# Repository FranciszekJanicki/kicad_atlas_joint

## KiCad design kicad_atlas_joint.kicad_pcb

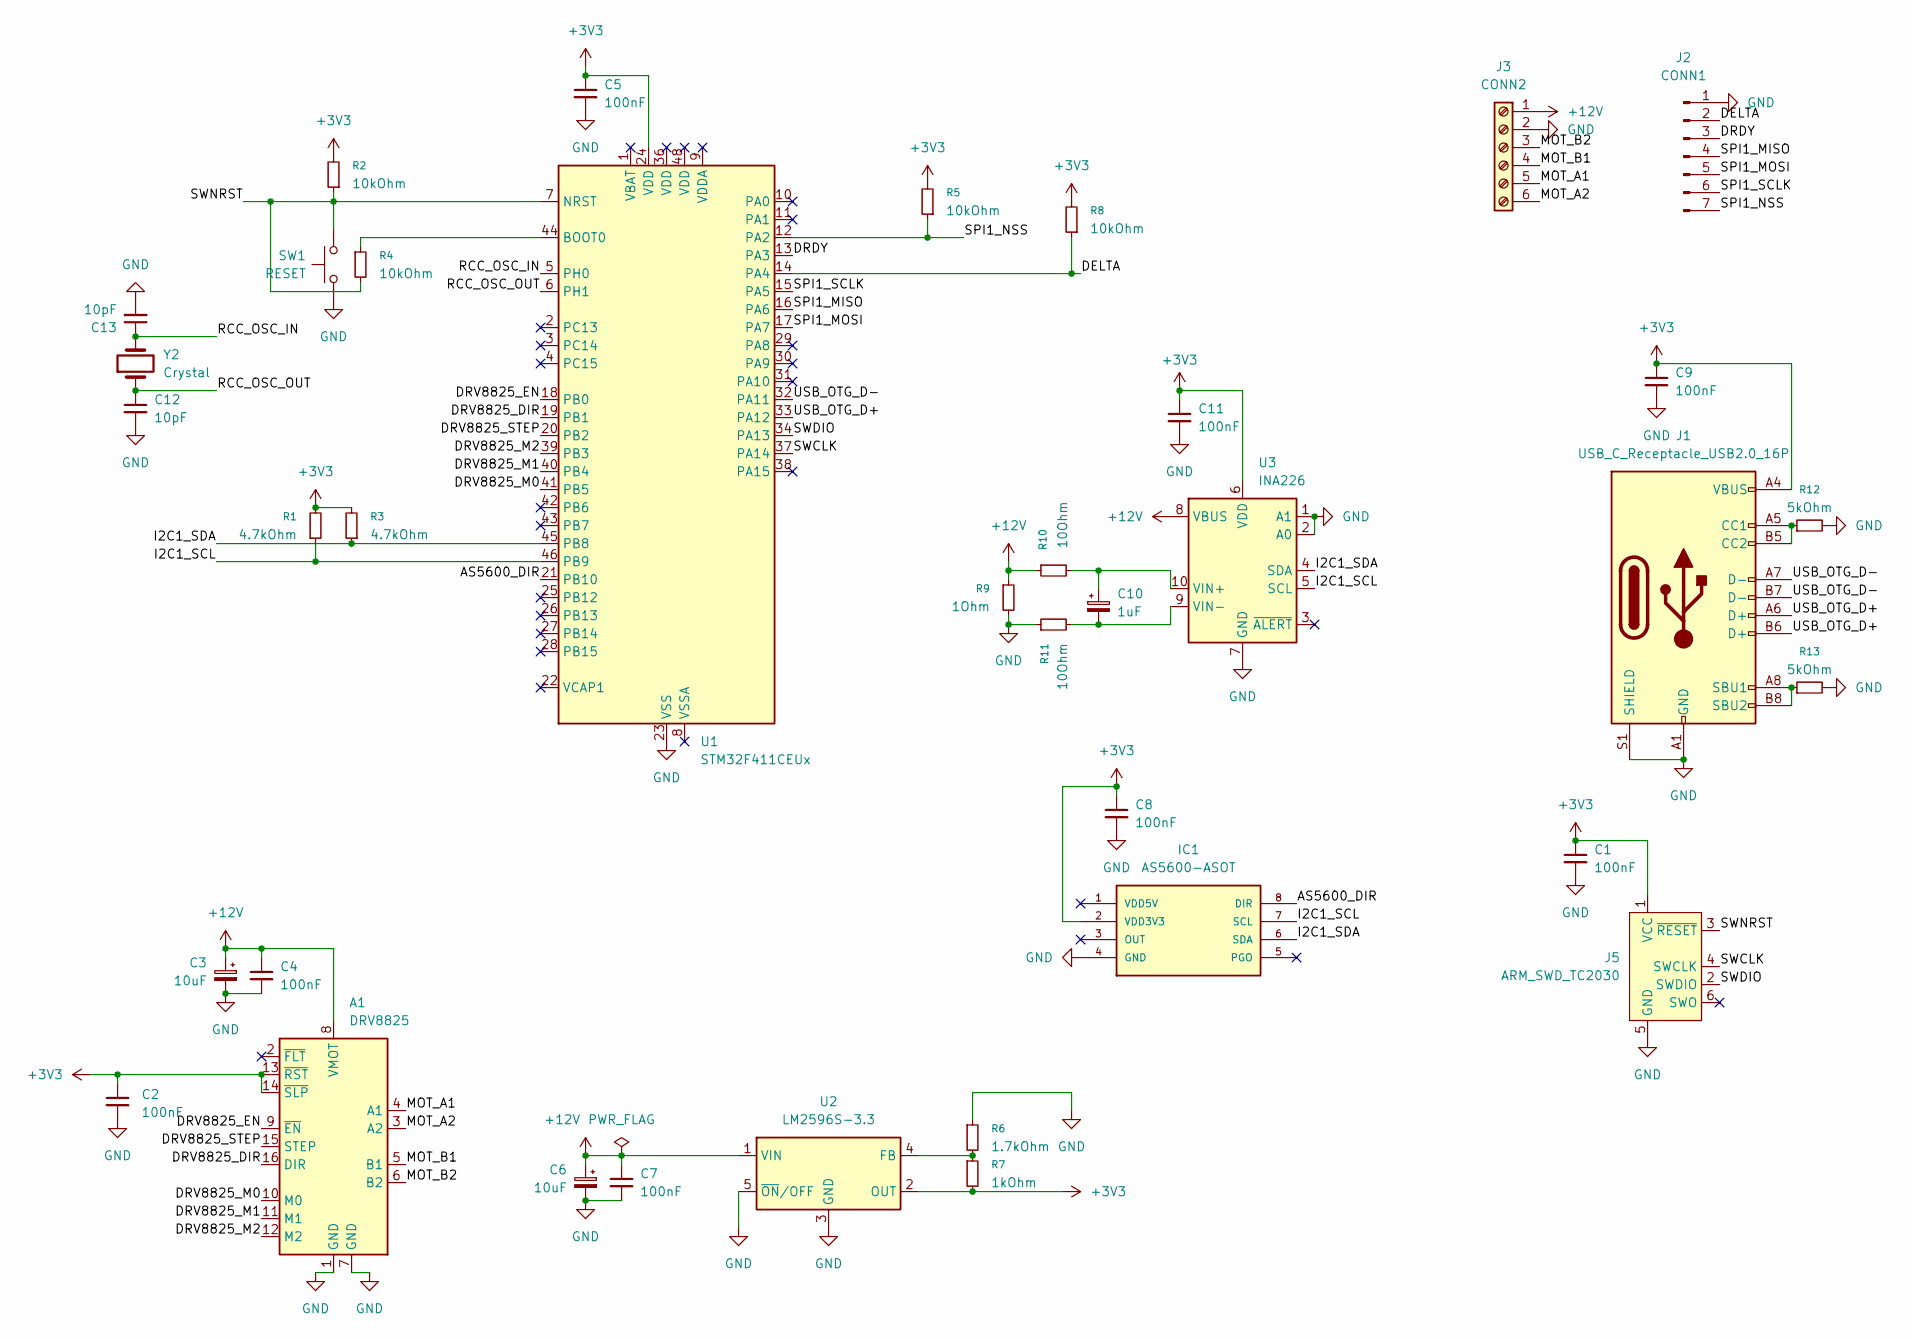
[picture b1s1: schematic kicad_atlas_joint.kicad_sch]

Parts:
A1: DRV8825; Pololu_Breakout-16_15.2x20.3mm
C1, C2, C4, C5, C7, C8, C9, C11: 100nF; C_0201_0603Metric_Pad0.64x0.40mm_HandSolder
C3, C6: 10uF; C_0201_0603Metric_Pad0.64x0.40mm_HandSolder
C10: 1uF; C_0201_0603Metric_Pad0.64x0.40mm_HandSolder
C12, C13: 10pF; C_0201_0603Metric_Pad0.64x0.40mm_HandSolder
IC1: AS5600-ASOT; SOIC127P600X175-8N; MOUSER_PART_NUMBER 985-AS5600-ASOT
J1: USB_C_Receptacle_USB2.0_16P; USB_C_Receptacle_JAE_DX07S016JA1R1500
J2: CONN1; JST_SHL_SM07B-SHLS-TF_1x07-1MP_P1.00mm_Horizontal
J3: CONN2; TerminalBlock_Xinya_XY308-2.54-6P_1x06_P2.54mm_Horizontal
J5: ARM_SWD_TC2030; Tag-Connect_TC2030-IDC-FP_2x03_P1.27mm_Vertical
R1, R3: 4.7kOhm; R_0201_0603Metric
R2, R4, R5, R8: 10kOhm; R_0201_0603Metric
R6: 1.7kOhm; R_0201_0603Metric
R7: 1kOhm; R_0201_0603Metric
R9: 1Ohm; R_0201_0603Metric
R10, R11: 10Ohm; R_0201_0603Metric
R12, R13: 5kOhm; R_0201_0603Metric
SW1: RESET; R_0201_0603Metric
U1: STM32F411CEUx; QFN-48-1EP_7x7mm_P0.5mm_EP5.6x5.6mm
U2: LM2596S-3.3; TO-263-5_TabPin3
U3: INA226; VSSOP-10_3x3mm_P0.5mm
Y2: Crystal; Crystal_AT310_D3.0mm_L10.0mm_Horizontal

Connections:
+3V3: A1.13 (~RST), A1.14 (~SLP), C1.1, C2.1, C5.1, C8.1, C9.1, C11.1, IC1.2 (VDD3V3), J1.A4 (VBUS), J1.A9 (VBUS), J1.B4 (VBUS), J1.B9 (VBUS), J5.1 (VCC), R1.2, R2.2, R3.2, R5.2, R7.2, R8.2, U1.24 (VDD), U2.2 (OUT), U3.6 (VDD)
+12V: A1.8 (VMOT), C3.1, C4.1, C6.1, C7.1, J3.1, R9.1, R10.1, U2.1 (VIN), U3.8 (VBUS)
/AS5600_DIR: IC1.8 (DIR), U1.21 (PB10)
/DELTA: J2.2, R8.1, U1.14 (PA4)
/DRDY: J2.3, U1.13 (PA3)
/DRV8825_DIR: A1.16 (DIR), U1.19 (PB1)
/DRV8825_EN: A1.9 (~EN), U1.18 (PB0)
/DRV8825_M0: A1.10 (M0), U1.41 (PB5)
/DRV8825_M1: A1.11 (M1), U1.40 (PB4)
/DRV8825_M2: A1.12 (M2), U1.39 (PB3)
/DRV8825_STEP: A1.15 (STEP), U1.20 (PB2)
/I2C1_SCL: IC1.7 (SCL), R1.1, U1.46 (PB9), U3.5 (SCL)
/I2C1_SDA: IC1.6 (SDA), R3.1, U1.45 (PB8), U3.4 (SDA)
/MOT_A1: A1.4 (A1), J3.5
/MOT_A2: A1.3 (A2), J3.6
/MOT_B1: A1.5 (B1), J3.4
/MOT_B2: A1.6 (B2), J3.3
/RCC_OSC_IN: C13.1, U1.5 (PH0), Y2.2
/RCC_OSC_OUT: C12.1, U1.6 (PH1), Y2.1
/SPI1_MISO: J2.4, U1.16 (PA6)
/SPI1_MOSI: J2.5, U1.17 (PA7)
/SPI1_NSS: J2.7, R5.1, U1.12 (PA2)
/SPI1_SCLK: J2.6, U1.15 (PA5)
/SWCLK: J5.4 (SWCLK), U1.37 (PA14)
/SWDIO: J5.2 (SWDIO), U1.34 (PA13)
/SWNRST: J5.3 (~RESET), R2.1, R4.2, SW1.1, U1.7 (NRST)
/USB_OTG_D+: J1.A6 (D+), J1.B6 (D+), U1.33 (PA12)
/USB_OTG_D-: J1.A7 (D-), J1.B7 (D-), U1.32 (PA11)
GND: A1.1 (GND), A1.7 (GND), C1.2, C2.2, C3.2, C4.2, C5.2, C6.2, C7.2, C8.2, C9.2, C11.2, C12.2, C13.2, IC1.4 (GND), J1.A1 (GND), J1.A12 (GND), J1.B1 (GND), J1.B12 (GND), J1.S1 (SHIELD), J2.1, J3.2, J5.5 (GND), R6.1, R9.2, R11.1, R12.2, R13.2, SW1.2, U1.23 (VSS), U1.35 (VSS), U1.47 (VSS), U1.49 (VSS), U2.3 (GND), U2.5 (~ON/OFF), U3.1 (A1), U3.2 (A0), U3.7 (GND)
unnamed: J1.A5 (CC1), J1.B5 (CC2), R12.1
unnamed: J1.A8 (SBU1), J1.B8 (SBU2), R13.1
unnamed: R4.1, U1.44 (BOOT0)
unnamed: R6.2, R7.1, U2.4 (FB)
unnamed: C10.1, R10.2, U3.10 (VIN+)
unnamed: C10.2, R11.2, U3.9 (VIN-)

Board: 2 copper layers, 37 parts (1 on the bottom side), 35 nets, no tracks yet.
